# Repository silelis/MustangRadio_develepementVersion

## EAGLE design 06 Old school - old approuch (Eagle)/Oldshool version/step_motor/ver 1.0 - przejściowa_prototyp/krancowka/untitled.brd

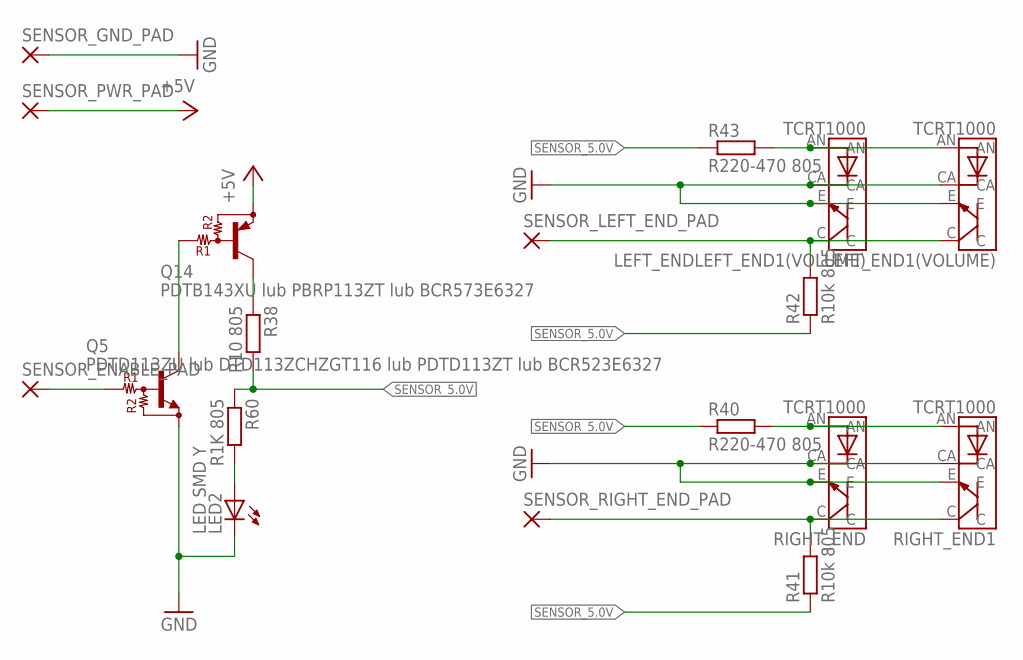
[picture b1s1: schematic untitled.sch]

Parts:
LED2: LED SMD Y; CHIP-LED0805
LEFT_END1(VOLUME): TCRT1000
LEFT_ENDLEFT_END1(VOLUME): TCRT1000
Q5: PDTD113ZU lub DTD113ZCHZGT116 lub PDTD113ZT lub B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; SOT-23
Q14: PDTB143XU lub PBRP113ZT lub BCR573E6327; SOT-23
R38: R10 805; R0805
R40, R43: R220-470 805; M0805
R41, R42: R10k 805; M0805
R60: R1K 805; R0805
RIGHT_END, RIGHT_END1: TCRT1000
SENSOR_ENABLE_PAD: SMD2; SMD1,27-2,54
SENSOR_GND_PAD: SMD2; SMD1,27-2,54
SENSOR_LEFT_END_PAD: SMD2; SMD1,27-2,54
SENSOR_PWR_PAD: SMD2; SMD1,27-2,54
SENSOR_RIGHT_END_PAD: SMD2; SMD1,27-2,54

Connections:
+5V: Q14.2 (E), SENSOR_PWR_PAD.1
END_SENSOR_ENABLE: Q5.1 (B), SENSOR_ENABLE_PAD.1
GND: LED2.C, LEFT_END1(VOLUME).CA, LEFT_END1(VOLUME).E, LEFT_ENDLEFT_END1(VOLUME).CA, LEFT_ENDLEFT_END1(VOLUME).E, Q5.2 (E), RIGHT_END.CA, RIGHT_END.E, RIGHT_END1.CA, RIGHT_END1.E, SENSOR_GND_PAD.1
unnamed: Q5.3 (C), Q14.1 (B)
unnamed: R40.2, RIGHT_END.AN, RIGHT_END1.AN
unnamed: Q14.3 (C), R38.1
unnamed: LEFT_END1(VOLUME).AN, LEFT_ENDLEFT_END1(VOLUME).AN, R43.2
unnamed: LEFT_END1(VOLUME).C, LEFT_ENDLEFT_END1(VOLUME).C, R42.2, SENSOR_LEFT_END_PAD.1
unnamed: R41.2, RIGHT_END.C, RIGHT_END1.C, SENSOR_RIGHT_END_PAD.1
unnamed: LED2.A, R60.2
SENSOR_5.0V: R38.2, R40.1, R41.1, R42.1, R43.1, R60.1

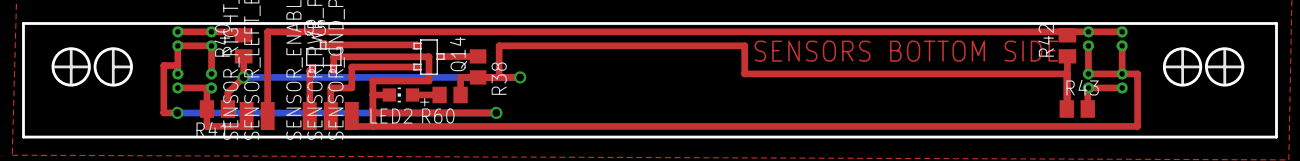
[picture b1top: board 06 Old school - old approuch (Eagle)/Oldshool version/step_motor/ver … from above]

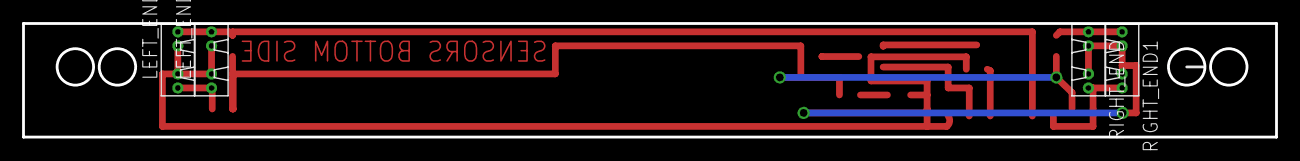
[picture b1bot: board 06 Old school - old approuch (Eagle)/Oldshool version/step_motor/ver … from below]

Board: 2 copper layers, 113.4 x 10.3 mm, 18 parts (4 on the bottom side), 11 nets.

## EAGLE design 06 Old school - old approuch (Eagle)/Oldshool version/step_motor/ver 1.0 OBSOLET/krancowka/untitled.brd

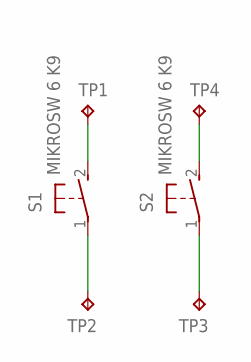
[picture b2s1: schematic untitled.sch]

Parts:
S1, S2: MIKROSW 6 K9; MIKROSW_6_K9
TP1, TP2, TP3, TP4: TPPAD1-13Y; P1-13Y

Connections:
unnamed: S1.2 (S), TP1.TP
unnamed: S1.1, TP2.TP
unnamed: S2.1, TP3.TP
unnamed: S2.2 (S), TP4.TP

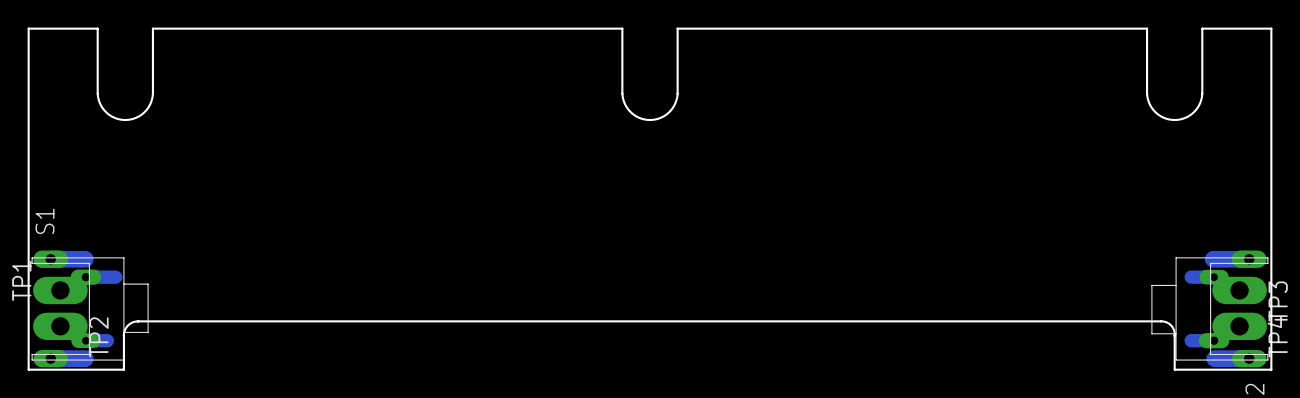
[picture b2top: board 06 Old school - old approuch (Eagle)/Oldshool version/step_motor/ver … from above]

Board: 2 copper layers, 90.0 x 24.7 mm, 6 parts (0 on the bottom side), 4 nets.

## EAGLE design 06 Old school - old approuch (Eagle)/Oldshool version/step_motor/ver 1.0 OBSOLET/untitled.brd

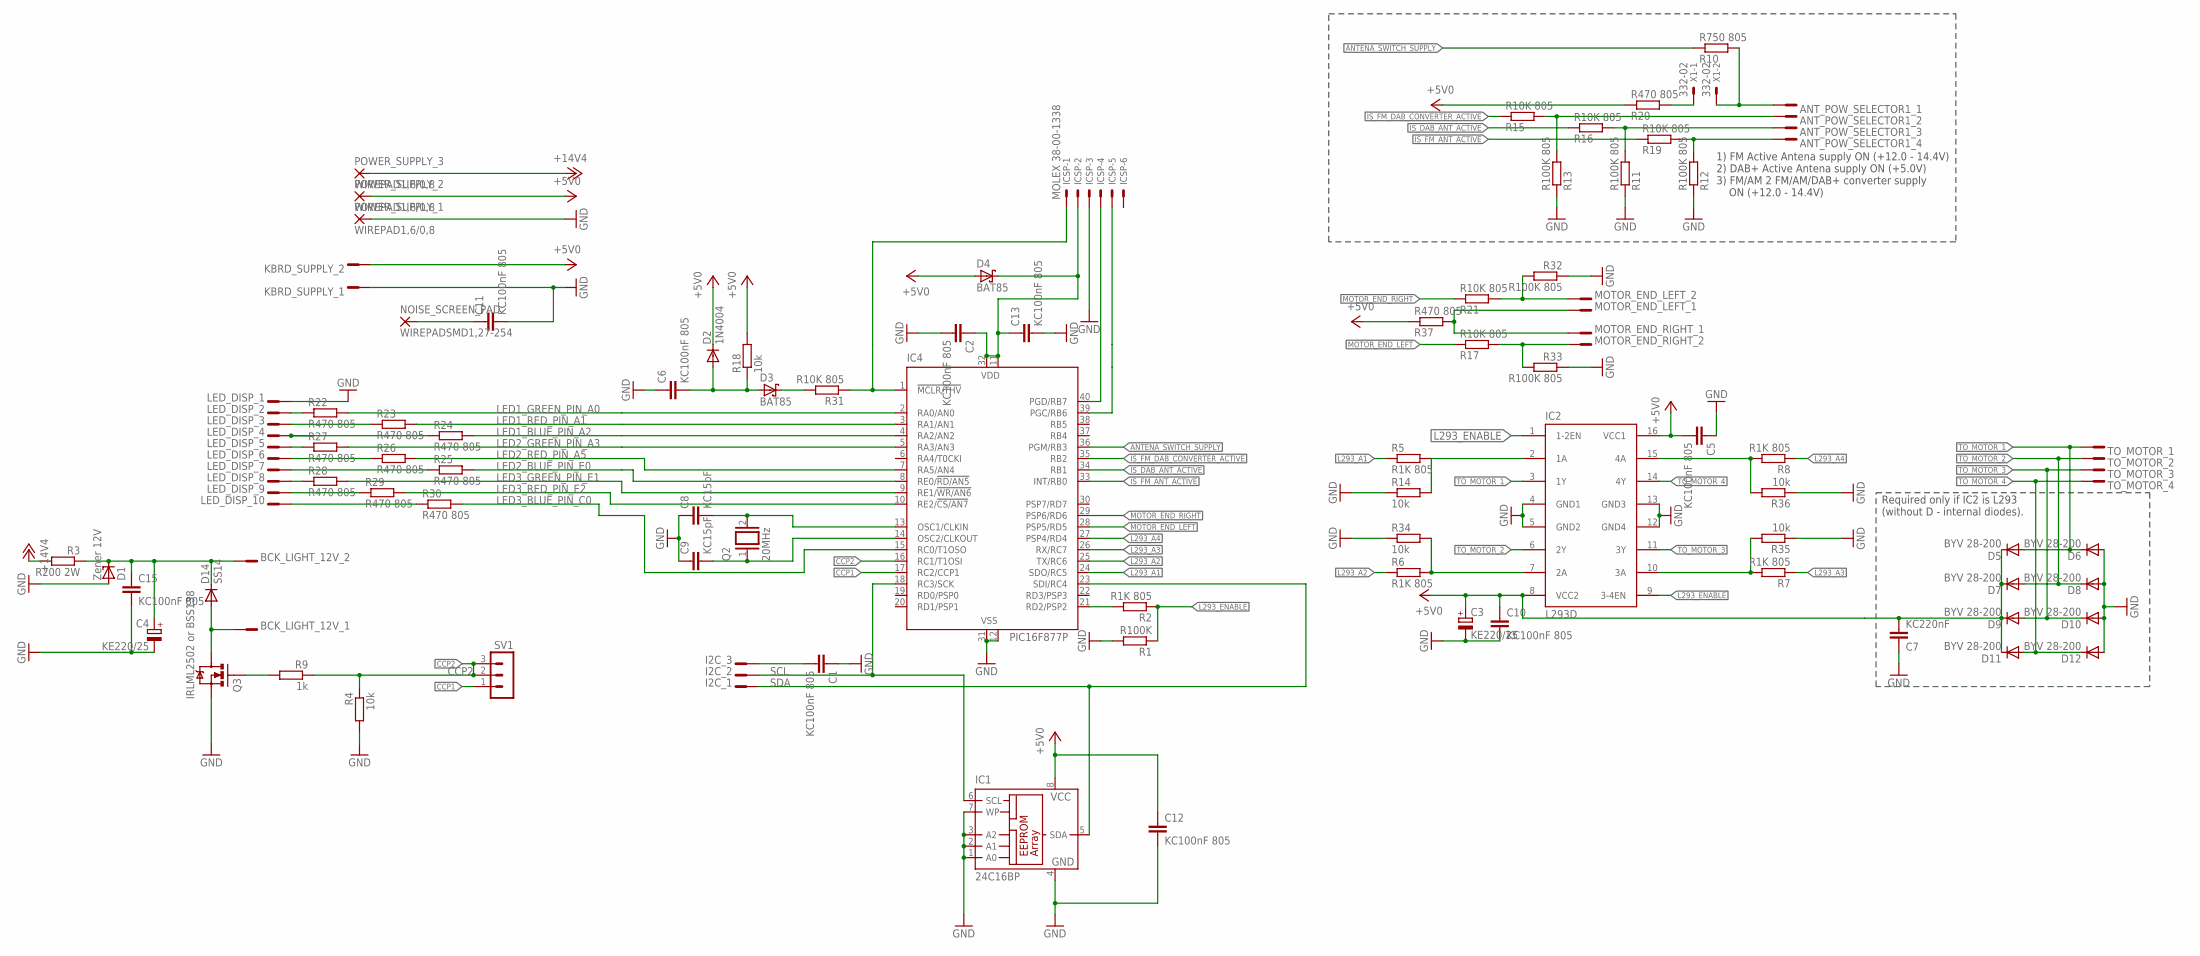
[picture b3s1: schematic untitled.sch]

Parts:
ANT_POW_SELECTOR1: JST_4_PIN_B4B-PH-KS; B4B-PH-KS
BCK_LIGHT_12V: JST_2_PIN_B2B-XH-A; B2B-XH-A
C1, C2, C5, C6, C10, C11, C12, C13, C15: KC100nF 805; C0805
C3: KE220/25; E3,5-8
C4: KE220/25; TT2D7
C7: KC220nF; C050-030X075
C8, C9: KC15pF; C025-030X050
D1: Zener 12V; ZDIO-5
D2: 1N4004; DO41-7.6
D3, D4: BAT85; DO34-5
D5, D6, D7, D8, D9, D10, D11, D12: BYV 28-200; SOD64-10
D14: SS14; SMB
I2C: JST_3_PIN_B3B-PH-KS; B3B-PH-KS
IC1: 24C16BP; DIL8
IC2: L293D; DIL16
IC4: PIC16F877P; DIL40
ICSP: MOLEX 38-00-1338; 6410-06
KBRD_SUPPLY: JST_2_PIN_B2B-PH-KS; B2B-PH-KS
LED_DISP: JST_10_PIN_B10B-PH-KS; B10B-PH-KS
MOTOR_END_LEFT: JST_2_PIN_B2B-PH-KS; B2B-PH-KS
MOTOR_END_RIGHT: JST_2_PIN_B2B-PH-KS; B2B-PH-KS
NOISE_SCREEN_PAD: WIREPADSMD1,27-254; SMD1,27-2,54
POWER_SUPPLY_1, POWER_SUPPLY_2, POWER_SUPPLY_3: WIREPAD1,6/0,8; 1,6/0,8
Q2: 20MHz; QS
Q3: IRLML2502 or BSS138; SOT23-3
R1: R100K; 0204/7
R2, R5, R6, R7, R8: R1K 805; R0805
R3: R200 2W; 0207/12
R4: 10k; M0805
R9: 1k; 0207/12
R10: R750 805; R0805
R11, R12, R13, R32, R33: R100K 805; R0805
R14: 10k; 0204V
R15, R16, R17, R19, R21, R31: R10K 805; R0805
R18: 10k; R0805
R20, R22, R23, R24, R25, R26, R27, R28, R29, R30, R37: R470 805; R0805
R34: 10k; 0204/5
R35, R36: 10k; 0204/7
SV1: MA03-1
TO_MOTOR: JST_4_PIN_B4B-XH-A; B4B-XH-A
X1: 332-02

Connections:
+5V: C3.+, C5.2, C7.2, C10.1, C12.1, D2.C, D4.A, D5.C, D7.C, D9.C, D11.C, IC1.8 (VCC), IC2.8 (VCC2), IC2.16 (VCC1), KBRD_SUPPLY.P$2, POWER_SUPPLY_2.1, R18.2, R20.1, R37.1
+14V4: POWER_SUPPLY_3.1, R3.2
ANTENA_SWITCH_SUPPLY: IC4.36 (PGM/RB3), R10.1
CCP1: IC4.17 (RC2/CCP1), SV1.1
CCP2: IC4.16 (RC1/T1OSI), R4.1, R9.1, SV1.2, SV1.3
GND: C1.1, C2.2, C3.-, C4.-, C5.1, C6.1, C7.1, C8.1, C9.1, C10.2, C11.2, C12.2, C13.2, C15.2, D1.A, D6.A, D8.A, D10.A, D12.A, IC1.1 (A0), IC1.2 (A1), IC1.3 (A2), IC1.4 (GND), IC1.7 (WP), IC2.4 (GND1), IC2.5 (GND2), IC2.12 (GND4), IC2.13 (GND3), IC4.12 (VSS), IC4.31 (VSS), ICSP.3, KBRD_SUPPLY.P$1, LED_DISP.P$1, POWER_SUPPLY_1.1, Q3.2 (S), R1.2, R4.2, R11.1, R12.1, R13.1, R14.1, R32.1, R33.1, R34.1, R35.1, R36.1
IS_DAB_ANT_ACTIVE: IC4.34 (RB1), R16.1
IS_FM_ANT_ACTIVE: IC4.33 (INT/RB0), R19.1
IS_FM_DAB_CONVERTER_ACTIVE: IC4.35 (RB2), R15.1
L293_A1: IC4.24 (SDO/RC5), R5.1
L293_A2: IC4.25 (TX/RC6), R6.1
L293_A3: IC4.26 (RX/RC7), R7.1
L293_A4: IC4.27 (PSP4/RD4), R8.1
L293_ENABLE: IC2.1 (1-2EN), IC2.9 (3-4EN), R1.1, R2.1
LED1_BLUE_PIN_A2: IC4.4 (RA2/AN2), R24.2
LED1_GREEN: LED_DISP.P$3, R23.1
LED1_GREEN_PIN_A0: IC4.2 (RA0/AN0), R22.2
LED1_RED: LED_DISP.P$4, R24.1
LED1_RED_PIN_A1: IC4.3 (RA1/AN1), R23.2
LED2_BLUE: LED_DISP.P$5, R27.1
LED2_BLUE_PIN_E0: IC4.8 (RE0/!RD/AN5), R25.2
LED2_GREEN: LED_DISP.P$6, R26.1
LED2_GREEN_PIN_A3: IC4.5 (RA3/AN3), R27.2
LED2_RED: LED_DISP.P$7, R25.1
LED2_RED_PIN_A5: IC4.7 (RA5/AN4), R26.2
LED3_BLUE: LED_DISP.P$8, R28.1
LED3_BLUE_PIN_C0: IC4.15 (RC0/T1OSO), R30.2
LED3_GREEN: LED_DISP.P$9, R29.1
LED3_GREEN_PIN_E1: IC4.9 (RE1/!WR/AN6), R28.2
LED3_RED: LED_DISP.P$10, R30.1
LED3_RED_PIN_E2: IC4.10 (RE2/!CS/AN7), R29.2
MOTOR_END_LEFT: IC4.28 (PSP5/RD5), R17.1
MOTOR_END_RIGHT: IC4.29 (PSP6/RD6), R21.1
unnamed: MOTOR_END_LEFT.P$1, MOTOR_END_RIGHT.P$1, R37.2
unnamed: Q3.1 (G), R9.2
unnamed: BCK_LIGHT_12V.P$1, D14.A, Q3.3 (D)
unnamed: R20.2, X1.1
unnamed: IC2.2 (1A), R5.2, R14.2
unnamed: IC2.7 (2A), R6.2, R34.2
unnamed: IC2.15 (4A), R8.2, R36.2
unnamed: C8.2, IC4.13 (OSC1/CLKIN), Q2.2
unnamed: MOTOR_END_RIGHT.P$2, R17.2, R33.2
unnamed: C1.2, I2C.P$3
unnamed: MOTOR_END_LEFT.P$2, R21.2, R32.2
unnamed: C9.2, IC4.14 (OSC2/CLKOUT), Q2.1
unnamed: BCK_LIGHT_12V.P$2, C4.+, C15.1, D1.C, D14.C, R3.1
unnamed: IC2.10 (3A), R7.2, R35.2
unnamed: ANT_POW_SELECTOR1.P$1, R10.2, X1.2
unnamed: IC4.21 (RD2/PSP2), R2.2
unnamed: LED_DISP.P$2, R22.1
unnamed: C2.1, C13.1, D4.C, IC4.11 (VDD), IC4.32 (VDD), ICSP.2
unnamed: C6.2, D2.A, D3.A, R18.1
unnamed: D3.C, R31.2
unnamed: IC4.1 (!MCLR/THV), ICSP.1, R31.1
NOISE_SCREEN: C11.1, NOISE_SCREEN_PAD.1
PGC: IC4.39 (PGC/RB6), ICSP.5
PGD: IC4.40 (PGD/RB7), ICSP.4
SCL: I2C.P$2, IC1.6 (SCL), IC4.18 (RC3/SCK)
SDA: I2C.P$1, IC1.5 (SDA), IC4.23 (SDI/RC4)
SWITCH_1: ANT_POW_SELECTOR1.P$4, R12.2, R19.2
SWITCH_2: ANT_POW_SELECTOR1.P$3, R11.2, R16.2
SWITCH_3: ANT_POW_SELECTOR1.P$2, R13.2, R15.2
TO_MOTOR_1: D5.A, D6.C, IC2.3 (1Y), TO_MOTOR.P$1
TO_MOTOR_2: D7.A, D8.C, IC2.6 (2Y), TO_MOTOR.P$2
TO_MOTOR_3: D9.A, D10.C, IC2.11 (3Y), TO_MOTOR.P$3
TO_MOTOR_4: D11.A, D12.C, IC2.14 (4Y), TO_MOTOR.P$4

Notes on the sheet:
Required only if IC2 is L293 (without D - internal diodes).
1) FM Active Antena supply ON (+12.0 - 14.4V) 2) DAB+ Active Antena supply ON (+5.0V) 3) FM/AM 2 FM/AM/DAB+ converter supply ON (+12.0 - 14.4V)

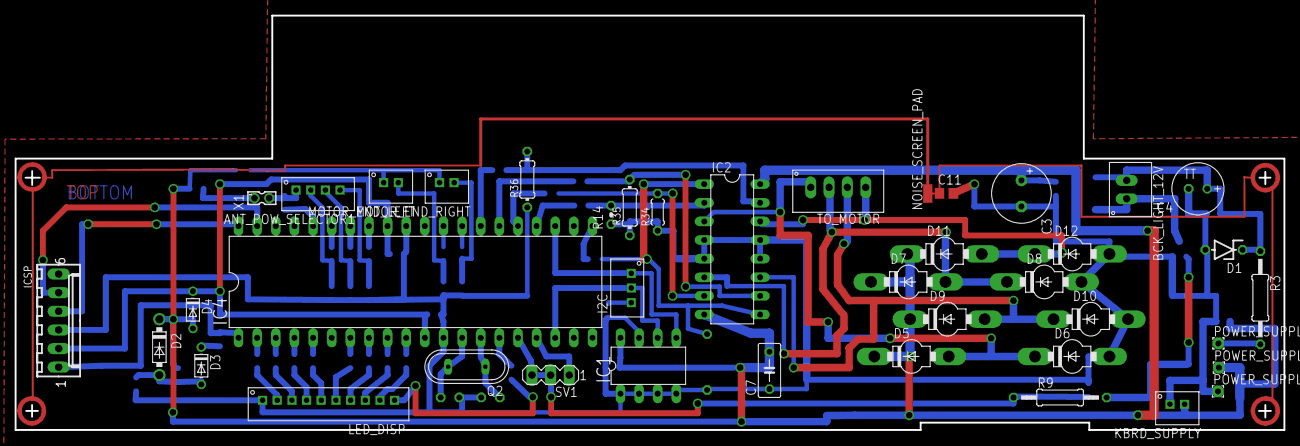
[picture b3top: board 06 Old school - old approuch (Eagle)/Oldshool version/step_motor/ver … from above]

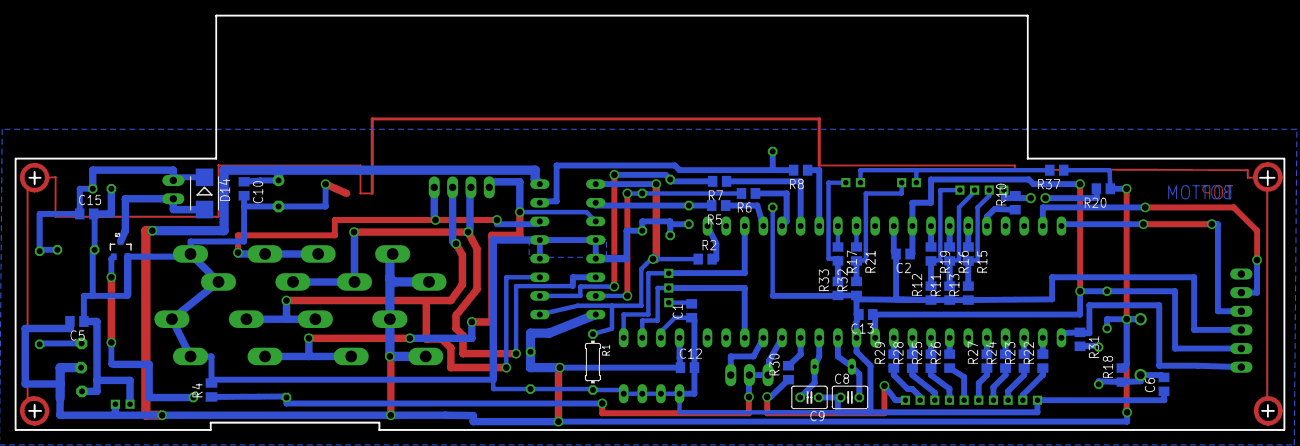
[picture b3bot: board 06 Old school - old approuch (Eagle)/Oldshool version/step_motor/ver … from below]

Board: 2 copper layers, 173.0 x 56.5 mm, 84 parts (43 on the bottom side), 66 nets.
